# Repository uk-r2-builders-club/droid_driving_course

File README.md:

This adds an automatic score board system to the UK R2D2 Builders driving course

Existing wired sensors can be replaced with wireless ones, talking back to a central access point and this code running on a Pi. The Pi can have a monitor on it set up to automatically display the scoreboard.

== Installation ==

''' sudo apt-get install git python3-pip python3-future python3-flask '''

''' sudo pip3 install flask-socketio '''

''' mkdir ~/.r2_builders '''

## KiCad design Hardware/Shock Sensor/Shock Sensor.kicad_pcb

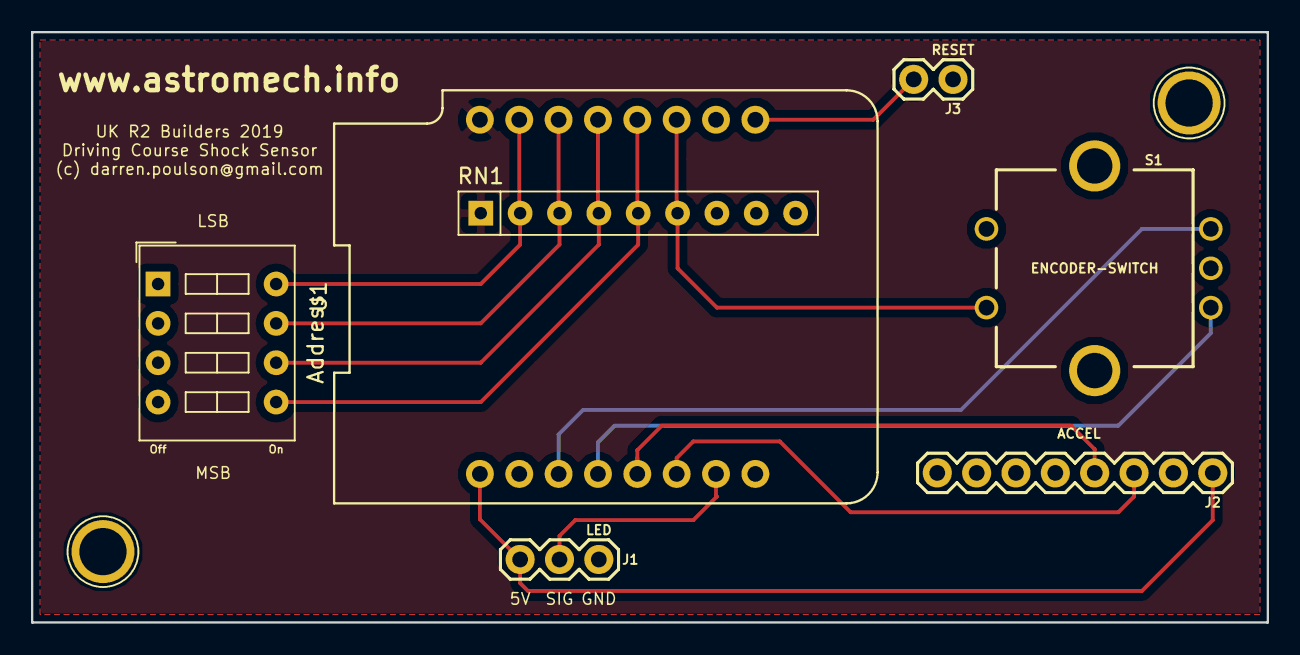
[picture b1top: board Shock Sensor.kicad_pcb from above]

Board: 2 copper layers, 79.8 x 38.1 mm, 7 parts (0 on the bottom side), 14 nets.

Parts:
Address: ADDRESS; SW_DIP_x4_W7.62mm_Slide
J1: LED; 1X03
J2: ACCEL; 1X08
J3: RESET; 1X02
RN1: R_Network08; R_Array_SIP9
S1: ENCODER-SWITCH; ROTARY_ENC_PLAIN
U1: WeMos_mini; wemos-d1-mini-with-pin-header-and-connector

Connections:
+3V3: RN1.1, U1.16
+5V: J1.3, J2.1, U1.1
GND: Address.1, Address.2, Address.3, Address.4, J1.1, J2.2, J3.1, S1.C, S1.SW+, U1.2
unnamed: J1.2, U1.7
unnamed: J2.3, U1.6
unnamed: J2.4, U1.5
unnamed: J3.2, U1.9
unnamed: Address.8, RN1.2, U1.15
unnamed: Address.7, RN1.3, U1.14
unnamed: Address.6, RN1.4, U1.13
unnamed: Address.5, RN1.5, U1.12
unnamed: RN1.6, S1.SW-, U1.11
unnamed: S1.A, U1.4
unnamed: S1.B, U1.3

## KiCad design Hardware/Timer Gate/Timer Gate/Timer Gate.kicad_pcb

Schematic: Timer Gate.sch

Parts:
J1: OUTPUT; 1X02
J2: SENSOR; 1X04
R1, R2: R; R_Axial_DIN0207_L6.3mm_D2.5mm_P7.62mm_Horizontal
U1: Trinket

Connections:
unnamed: J1.1, J2.4, R2.1, U1.2 (GND)
unnamed: J1.2, U1.8 (GPIO1)
unnamed: J1.3, J2.1, U1.10 (+USB)
unnamed: J2.2, U1.9 (GPIO0)
unnamed: J2.3, R1.2
unnamed: R1.1, R2.2, U1.7 (GPIO2)

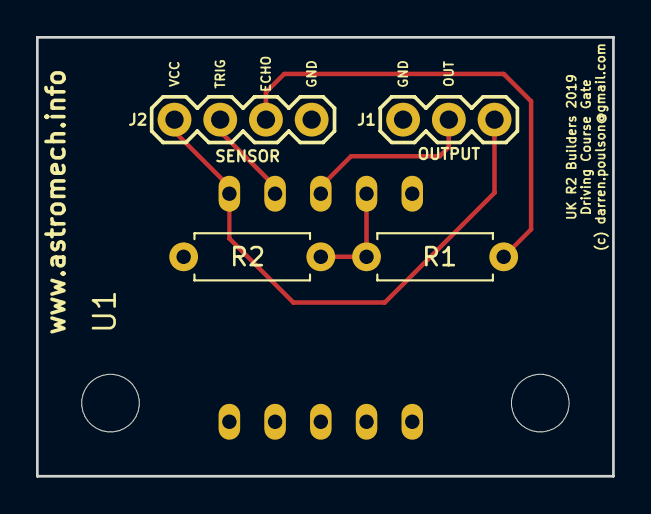
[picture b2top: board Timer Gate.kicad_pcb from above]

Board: 2 copper layers, 32.0 x 24.4 mm, 5 parts (0 on the bottom side), 6 nets.

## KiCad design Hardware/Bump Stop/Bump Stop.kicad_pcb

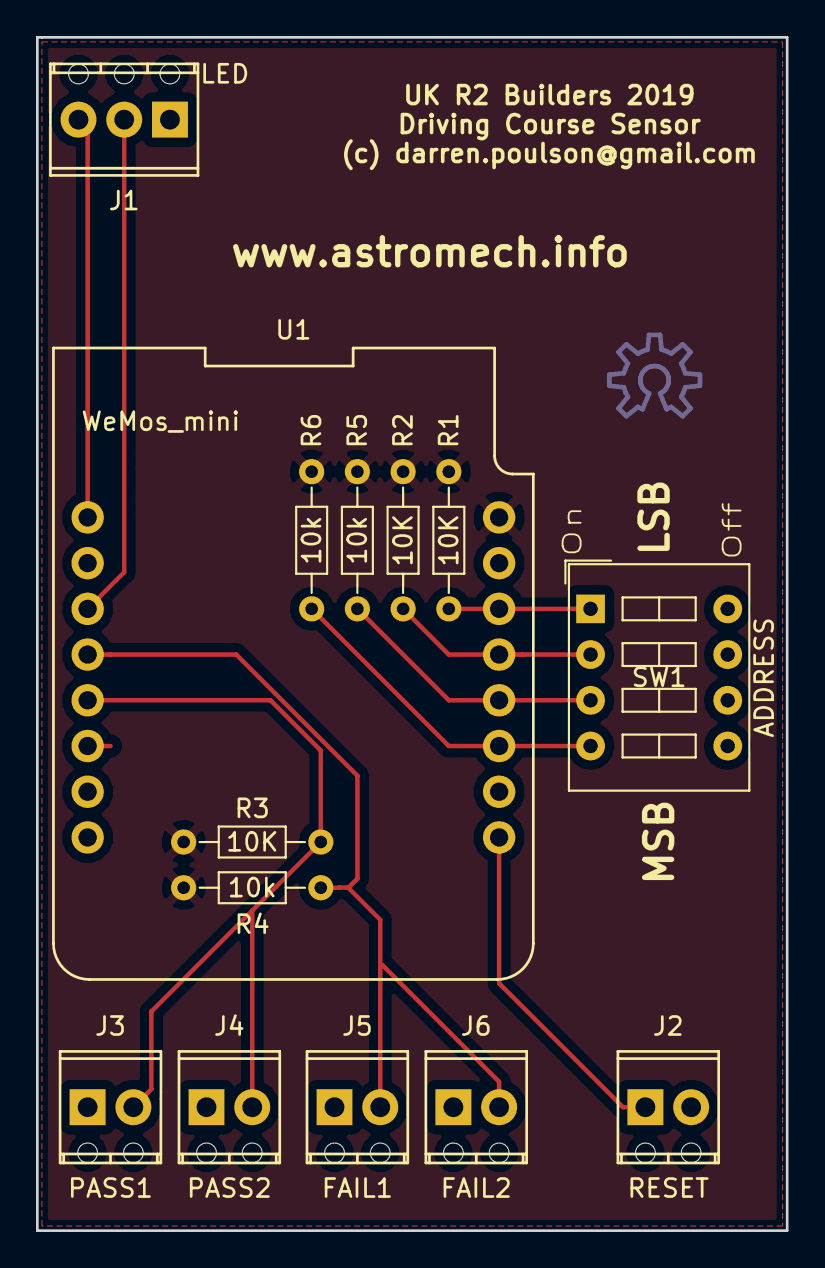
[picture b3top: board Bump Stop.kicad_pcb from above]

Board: 2 copper layers, 41.7 x 66.3 mm, 14 parts (0 on the bottom side), 11 nets.

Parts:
J1: LED; TerminalBlock_Phoenix_MPT-2.54mm_3pol
J2: RESET; TerminalBlock_Phoenix_MPT-2.54mm_2pol
J3: PASS1; TerminalBlock_Phoenix_MPT-2.54mm_2pol
J4: PASS2; TerminalBlock_Phoenix_MPT-2.54mm_2pol
J5: FAIL1; TerminalBlock_Phoenix_MPT-2.54mm_2pol
J6: FAIL2; TerminalBlock_Phoenix_MPT-2.54mm_2pol
R1, R2, R3: 10K; R_Axial_DIN0204_L3.6mm_D1.6mm_P7.62mm_Horizontal
R4, R5, R6: 10k; R_Axial_DIN0204_L3.6mm_D1.6mm_P7.62mm_Horizontal
SW1: ADDRESS; SW_DIP_x4_W7.62mm_Slide
U1: WeMos_mini; wemos-d1-mini-with-pin-header

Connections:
+3V3: R1.1, R2.1, R3.1, R4.1, R5.1, R6.1, U1.16
+5V: J1.3, U1.1
GND: J1.1, J2.2, J3.1, J4.1, J5.1, J6.1, SW1.5, SW1.6, SW1.7, SW1.8, U1.2
unnamed: J1.2, U1.3
unnamed: J2.1, U1.9
unnamed: J3.2, J4.2, R3.2, U1.5
unnamed: J5.2, J6.2, R4.2, U1.4
unnamed: R1.2, SW1.1, U1.14
unnamed: R2.2, SW1.2, U1.13
unnamed: R5.2, SW1.3, U1.12
unnamed: R6.2, SW1.4, U1.11

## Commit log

2019-02-01 Removed database from git repo
2019-02-01 Added README
2019-02-01 A few tweaks, and added Arduino code for RFID reader
2019-02-01 Added README for the RFID reader
2019-02-03 Lots of little tweaks, and cut down on some unneeded code in the RFID reader
2019-02-03 Added Gates to scoreboard, and a basic admin page
2019-02-04 RFID reader now has a buzzer, and all results can now be uploaded to the MOT site
2019-02-25 Updated RFID to use TTGO board with built in speaker and 1.4 inch TFT
2019-03-21 Added systemd service file
2019-03-21 Update of arduino code
2019-03-30 Added results page
2019-04-09 Bump sensor hardware and code update
2019-04-11 Load of updates, and some tools for reading RFID cards
2019-04-17 some tweaks to the rfid tools
2019-04-17 Updates to the bump sensor sketch and schematics
2019-05-09 Tweaks to arudino code
2019-05-12 Timing is now handled by the main clock, and its internal arduino. This is much more reliable
2019-05-12 Updates to main timer code, and added in course gate schematic and board
2019-05-15 Many updates to firmware, including receiving of UDP broadcasts
2019-05-15 Added broadcast ability, and will check if a run is the quickest on finish
2019-05-16 A few tweaks
2019-05-31 Added PCB for Timer Gate
2019-06-04 Added celebrations and contender page
2019-06-20 Will upload scores
2019-06-20 First code for strobe lights
2019-07-14 Updated course gate PCB, and updated the strobe code
2019-07-15 A few fixes
2019-07-15 Added ability to read DHCP leases to see connected devices
2019-07-15 Some clean up and a few tweaks to arduino code
2019-08-04 A few bug fixes
2019-08-04 Work on Strobe
2019-08-08 Added an RFID tag writer
2019-08-12 Added today results page, and fixed bug where penalties were able to be added even after the run had finished
2019-08-12 Added initial structure for Shock Sensor
2019-08-13 Added config options to the database, rather than an ini file. Also started on adding different course types
2019-08-13 Added audio library (from r2_control) and now and failed gate sets off a siren
2019-08-14 Added support for switching course layouts
2019-09-19 A few tweaks and comments to arduino code. Also started on shock sensor code
2019-09-20 Bunch of work on the shock sensor. Calibration works, and fixed a math overflow issue
2019-10-03 Updates to PCB and code for shock sensors
2022-05-18 Bunch of fixes, and moved bootstrap and JS requirements into repo for offline use
2022-07-24 Updates for pulling in members and droids
2022-08-10 Bunch of updates. Start of tag writer, and updates to contender page to use datatables
2022-08-15 Some emergency fixes done at DBUK 2022
2022-08-15 Fixes to the course upload to the portal.
2025-08-12 Updated bump stops
